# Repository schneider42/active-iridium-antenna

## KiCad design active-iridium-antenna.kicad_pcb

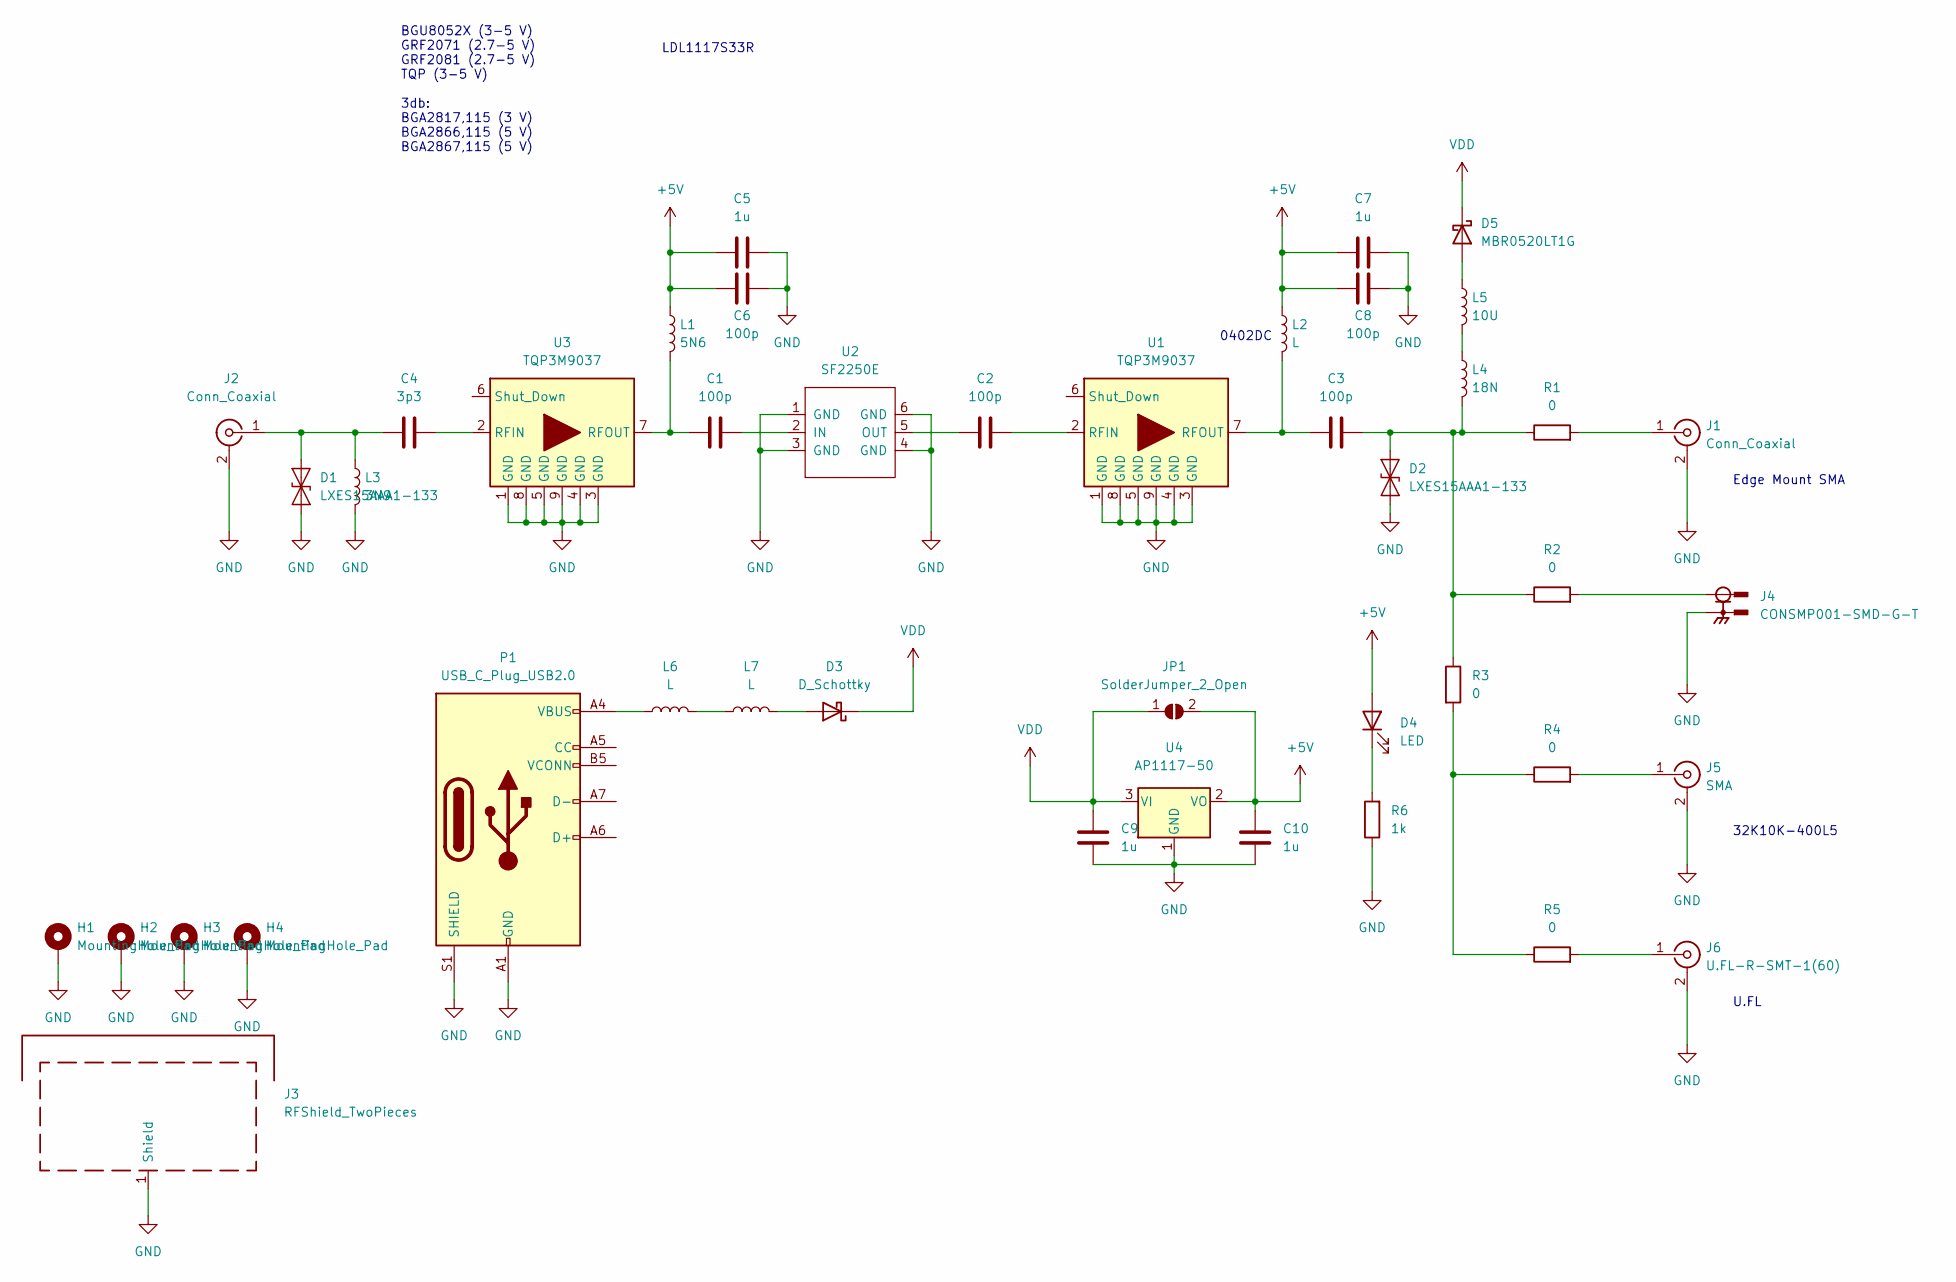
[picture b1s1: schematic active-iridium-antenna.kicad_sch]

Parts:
C1, C2, C3: 100p; C_0402_1005Metric
C4: 3p3; C_0402_1005Metric
C5, C7, C9, C10: 1u; C_0603_1608Metric
C6, C8: 100p; C_0603_1608Metric
D1, D2: LXES15AAA1-133; D_0402_1005Metric
D3: D_Schottky; D_SOD-123
D4: LED; D_0603_1608Metric
D5: MBR0520LT1G; D_SOD-123
H1, H2, H3, H4: MountingHole_Pad; MountingHole_3.2mm_M3_Pad_Via
J1: Conn_Coaxial; SMA_Samtec_SMA-J-P-X-ST-EM1_EdgeMount
J2: Conn_Coaxial; SMA_Amphenol_901-144_Vertical
J3: RFShield_TwoPieces; Laird_Technologies_BMI-S-203-F_26.21x26.21mm
J4: CONSMP001-SMD-G-T; LINX_CONSMP001-SMD-G-T; PARTREV A
J5: SMA; 32K10K-400L5
J6: U.FL-R-SMT-1(60); U.FL_Hirose_U.FL-R-SMT-1_Vertical
JP1: SolderJumper_2_Open; SolderJumper-2_P1.3mm_Open_Pad1.0x1.5mm
L1: 5N6; L_0402_1005Metric
L2, L6: L; L_0402_1005Metric
L3: 3N9; L_0402_1005Metric
L4: 18N; L_0402_1005Metric
L5: 10U; L_0805_2012Metric
L7: L; L_0805_2012Metric
P1: USB_C_Plug_USB2.0; USB_C_Receptacle_HRO_TYPE-C-31-M-12
R1, R2, R3, R4, R5: 0; R_0402_1005Metric
R6: 1k; R_0402_1005Metric
U1, U3: TQP3M9037; DFN-8-1EP_2x2mm_P0.5mm_EP0.7x1.6mm
U2: SF2250E; DCC6C
U4: AP1117-50; SOT-223-3_TabPin2

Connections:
+5V: C5.1, C6.1, C7.1, C8.1, C10.2, D4.2 (A), JP1.2 (B), L1.1, L2.1, U4.2 (VO)
GND: C5.2, C6.2, C7.2, C8.2, C9.1, C10.1, D1.1 (A1), D2.1 (A1), H1.1, H2.1, H3.1, H4.1, J1.2 (Ext), J2.2 (Ext), J3.1 (Shield), J4.S1, J5.2 (Ext), J6.2 (Ext), L3.2, P1.A1 (GND), P1.A12 (GND), P1.B1 (GND), P1.B12 (GND), P1.S1 (SHIELD), R6.1, U1.1 (GND), U1.3 (GND), U1.4 (GND), U1.5 (GND), U1.8 (GND), U1.9 (GND), U2.1 (GND), U2.3 (GND), U2.4 (GND), U2.6 (GND), U3.1 (GND), U3.3 (GND), U3.4 (GND), U3.5 (GND), U3.8 (GND), U3.9 (GND), U4.1 (GND)
unnamed: C1.1, L1.2, U3.7 (RFOUT)
unnamed: C1.2, U2.2 (IN)
unnamed: C2.1, U2.5 (OUT)
unnamed: C2.2, U1.2 (RFIN)
unnamed: C3.1, L2.2, U1.7 (RFOUT)
unnamed: C3.2, D2.2 (A2), L4.2, R1.1, R2.1, R3.1
unnamed: C4.1, D1.2 (A2), J2.1 (In), L3.1
unnamed: C4.2, U3.2 (RFIN)
unnamed: D3.2 (A), L7.2
unnamed: D4.1 (K), R6.2
unnamed: D5.2 (A), L5.1
unnamed: J1.1 (In), R1.2
unnamed: J4.1, R2.2
unnamed: J5.1 (In), R4.2
unnamed: J6.1 (In), R5.2
unnamed: L4.1, L5.2
unnamed: L6.1, P1.A4 (VBUS), P1.A9 (VBUS), P1.B4 (VBUS), P1.B9 (VBUS)
unnamed: L6.2, L7.1
unnamed: R3.2, R4.1, R5.1
VDD: C9.2, D3.1 (K), D5.1 (K), JP1.1 (A), U4.3 (VI)

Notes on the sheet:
Edge Mount SMA
LDL1117S33R
0402DC
U.FL
BGU8052X (3-5 V) GRF2071 (2.7-5 V) GRF2081 (2.7-5 V) TQP (3-5 V) 3db: BGA2817,115 (3 V) BGA2866,115 (5 V) BGA2867,115 (5 V)
32K10K-400L5

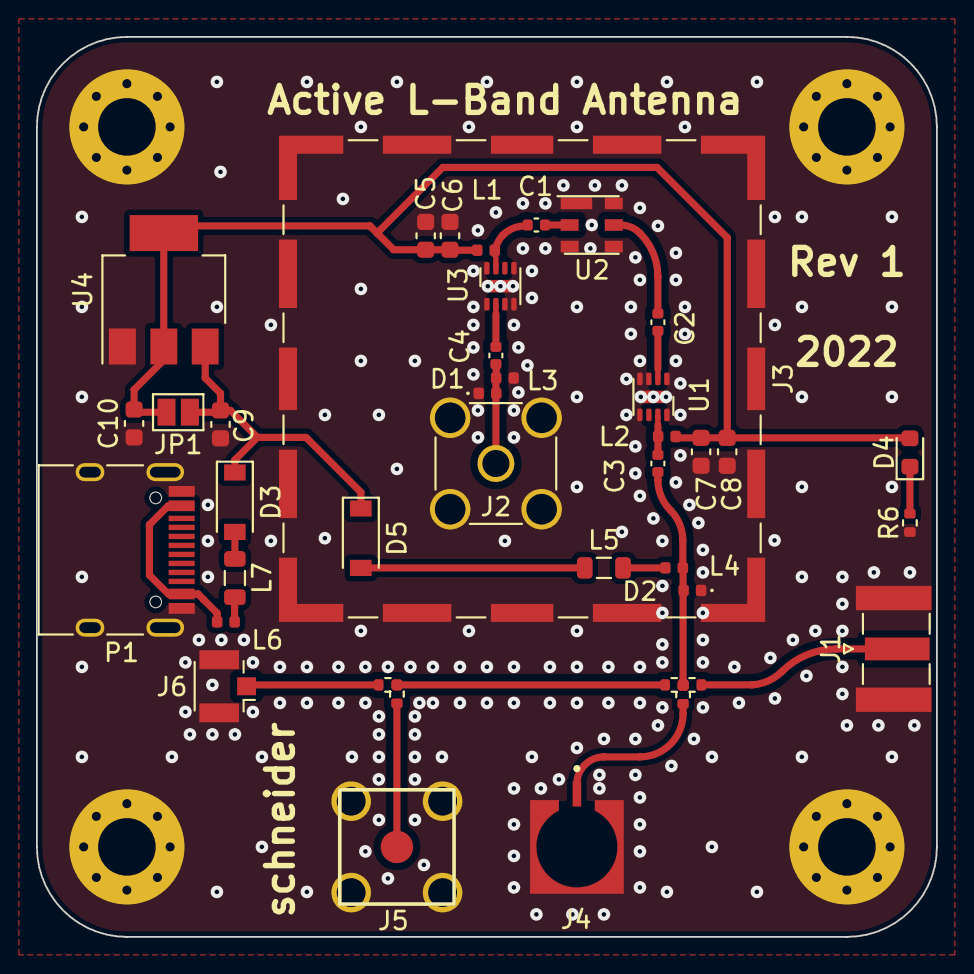
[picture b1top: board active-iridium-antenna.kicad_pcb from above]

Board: 4 copper layers, 50.0 x 50.0 mm, 44 parts (0 on the bottom side), 22 nets.
